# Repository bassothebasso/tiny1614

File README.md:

ATtiny1614 Breadboard friendly breakout board design. Not manufactured or tested (yet!)  

# Some features:  
- Attiny1614 (20MHz, 16KB Flash) microcontroller  
- USB-C Power supply w/ AP2112K LDO  
- UPDI Header for programming  
- 600mil DIP form factor  

# Pinout

The board pins are mapped 1:1 to the physical pins of the ATtiny1614 microcontroller

**Left Header**

| J3 Pin | Net / Label | ATtiny1614 Pin | Description |
| :--- | :--- | :--- | :--- |
| **1** | `+3V3` | 1 (VCC) | LDO Out |
| **2** | `PA4` | 2 | GPIO / Alt I2C SDA |
| **3** | `PA5` | 3 | GPIO |
| **4** | `PA6` | 4 | GPIO |
| **5** | `PA7` | 5 | GPIO |
| **6** | `PB3` | 6 | GPIO / Serial RX |
| **7** | `PB2` | 7 | GPIO / Serial TX |

**Right Header**

| J4 Pin | Net / Label | ATtiny1614 Pin | Description |
| :--- | :--- | :--- | :--- |
| **1** | `GND` | 14 (GND) | |
| **2** | `PA3` | 13 | GPIO / SPI SCK |
| **3** | `PA2` | 12 | GPIO / SPI MISO |
| **4** | `PA1` | 11 | GPIO / SPI MOSI / I2C SDA |
| **5** | `UPDI` | 10 (PA0) | UPDI Programming / Reset |
| **6** | `PB0` | 9 | GPIO / I2C SCL |
| **7** | `PB1` | 8 | GPIO / I2C SDA |

**Programming Header**

| J2 Pin | Function |
| :--- | :--- |
| **1** | `UPDI` (Connected to ATtiny Pin 10) |
| **2** | `+3V3` (Target Power) |
| **3** | `GND` (Common Ground) |

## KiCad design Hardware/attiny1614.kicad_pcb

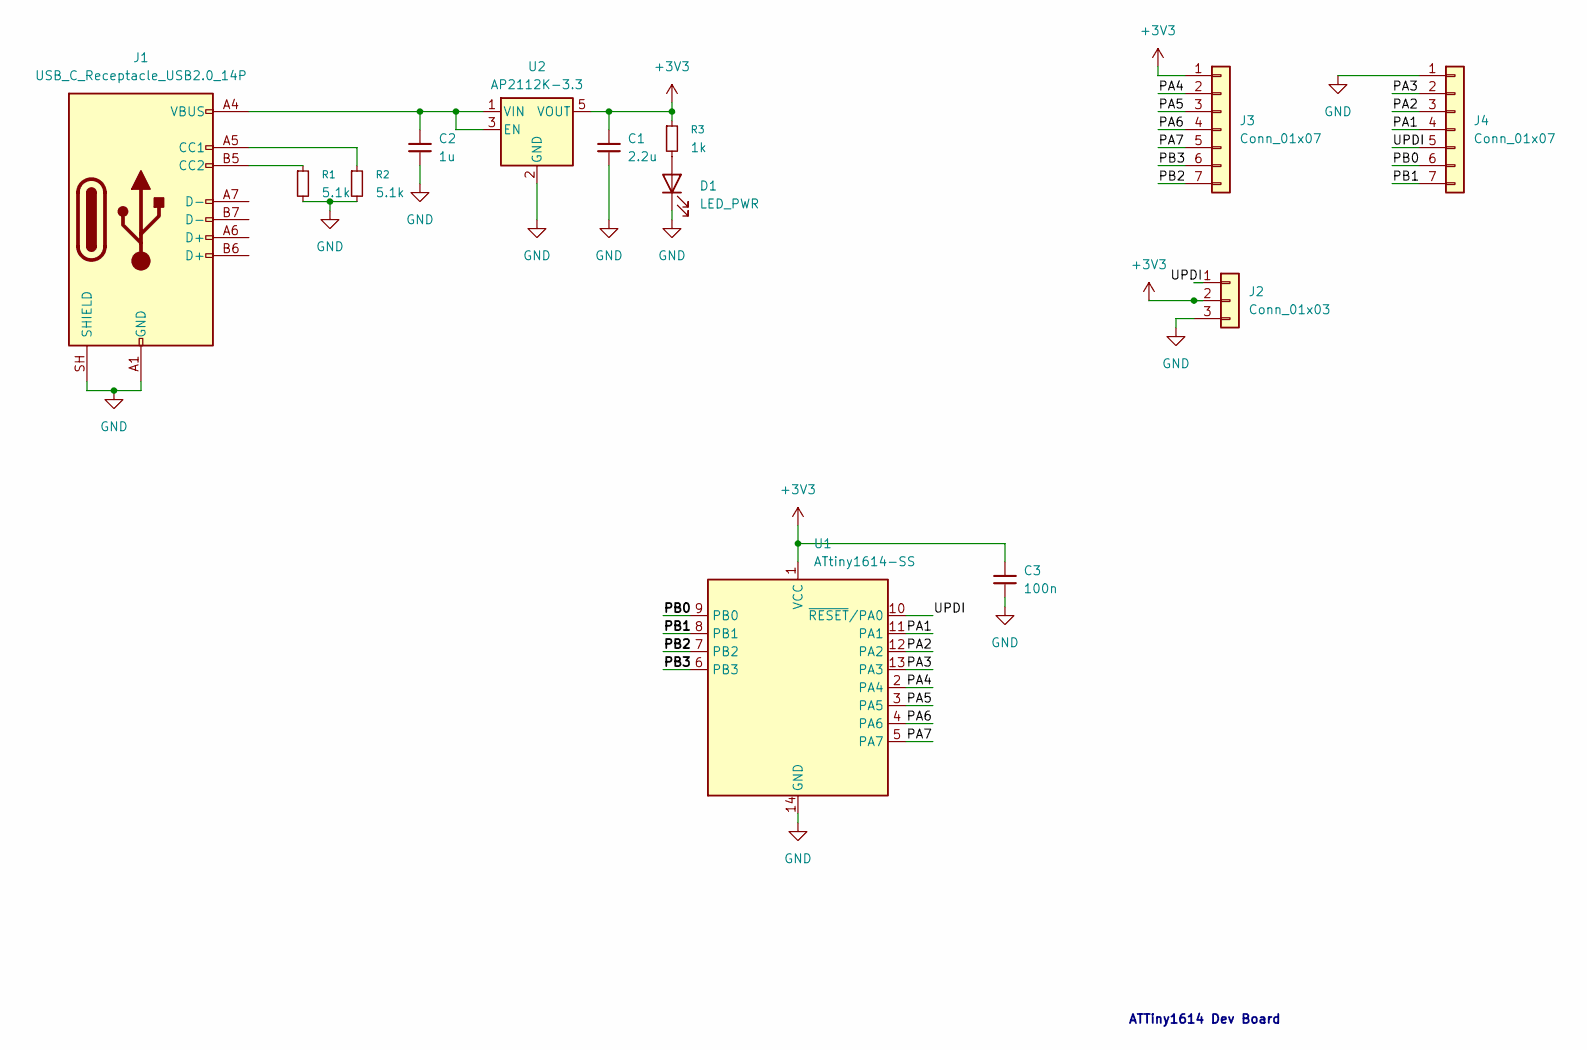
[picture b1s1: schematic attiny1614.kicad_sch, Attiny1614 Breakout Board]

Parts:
C1: 2.2u; C_0805_2012Metric_Pad1.18x1.45mm_HandSolder
C2: 1u; C_0805_2012Metric_Pad1.18x1.45mm_HandSolder
C3: 100n; C_0805_2012Metric_Pad1.18x1.45mm_HandSolder
D1: LED_PWR; LED_0805_2012Metric_Pad1.15x1.40mm_HandSolder
J1: USB_C_Receptacle_USB2.0_14P; USB_C_Receptacle_GCT_USB4105-xx-A_16P_TopMnt_Horizontal
J2: Conn_01x03; PinHeader_1x03_P2.54mm_Vertical
J3, J4: Conn_01x07; PinHeader_1x07_P2.54mm_Vertical
R1, R2: 5.1k; R_0805_2012Metric_Pad1.20x1.40mm_HandSolder
R3: 1k; R_0805_2012Metric_Pad1.20x1.40mm_HandSolder
U1: ATtiny1614-SS; SOIC-14_3.9x8.7mm_P1.27mm
U2: AP2112K-3.3; SOT-23-5_HandSoldering

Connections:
+3V3: C1.1, C3.1, J2.2, J3.1, R3.1, U1.1 (VCC), U2.5 (VOUT)
/PA1: J4.4, U1.11 (PA1)
/PA2: J4.3, U1.12 (PA2)
/PA3: J4.2, U1.13 (PA3)
/PA4: J3.2, U1.2 (PA4)
/PA5: J3.3, U1.3 (PA5)
/PA6: J3.4, U1.4 (PA6)
/PA7: J3.5, U1.5 (PA7)
/PB0: J4.6, U1.9 (PB0)
/PB1: J4.7, U1.8 (PB1)
/PB2: J3.7, U1.7 (PB2)
/PB3: J3.6, U1.6 (PB3)
/UPDI: J2.1, J4.5, U1.10 (~RESET/PA0)
GND: C1.2, C2.2, C3.2, D1.1 (K), J1.A1 (GND), J1.A12 (GND), J1.B1 (GND), J1.B12 (GND), J1.SH (SHIELD), J2.3, J4.1, R1.2, R2.2, U1.14 (GND), U2.2 (GND)
unnamed: D1.2 (A), R3.2
unnamed: J1.A5 (CC1), R2.1
unnamed: J1.B5 (CC2), R1.1
unnamed: C2.1, J1.A4 (VBUS), J1.A9 (VBUS), J1.B4 (VBUS), J1.B9 (VBUS), U2.1 (VIN), U2.3 (EN)

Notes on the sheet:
ATTiny1614 Dev Board

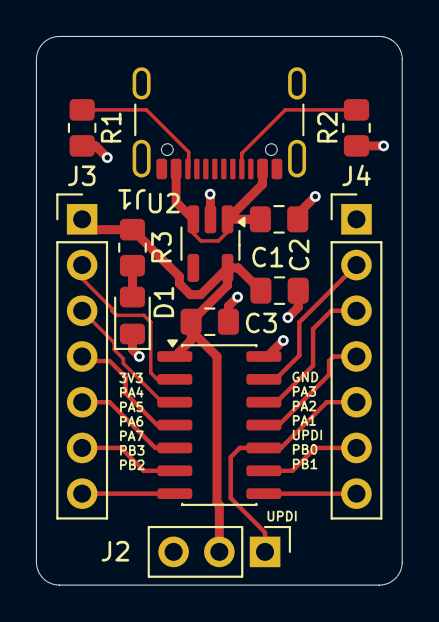
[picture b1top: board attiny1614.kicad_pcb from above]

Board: 2 copper layers, 20.3 x 30.5 mm, 13 parts (0 on the bottom side), 18 nets.
